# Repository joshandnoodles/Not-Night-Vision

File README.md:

## Objective

Using a PIC microcontroller and a non-contact infrared thermometer, MLX90614, an extremely low-cost thermal imaging system can be realized at a price point where thermal imaging data will be able to supplement and potentially replace traditional imaging solutions. The small, low cost MLX90614’s high precision measurements along with its narrow field of view (5&deg;) allow for cheap thermal data at a resolution that was previously unimaginable. Existing thermal imaging concepts using this sensor have already seen success[^ir_eye] [^arduino_ex]. However, the benefits of this sensor can be further exploited by using the following devices: mirrors to reduce vibrations and increase tracking speed, optics/diaphragm to precisely change pixel size for objects of varying size or varying distances, sampling and interpolation techniques, and low-level software changes to enhance sensor’s data collection. 

[^ir_eye]: http://spectrum.ieee.org/geek-life/hands-on/ir-eye

[^arduino_ex]: http://community.wolfram.com/groups/-/m/t/246929

[^pic_prod_list]: http://www.microchip.com/ParamChartSearch/Chart.aspx?branchID=8187

[^mlx_prod]: http://www.melexis.com/Infrared-Thermometer-Sensors/Infrared-Thermometer-Sensors/MLX90614-615.aspx

## Evaluation

At the conclusion of the project, success will be determined based on the system’s ability to complete the following tasks:

1. Reconstruct a 64-pixel image of a glass of heated water placed 10 meters away 
	- Temperature accuracy of +/1&deg;F
	- Image capture time <= 60 sec
2. Track a designated person moving at walking speed in a room maintaining tracking on that person even with other non-moving people in the room
	- *This will not necessarily be completed on the similar timeline as Task 1. It is an extra evaluation standard most likely meant for future time.*

## Project Needs

Hardware, tools, supplies anticipated for project:
- PIC microcontroller  with I2C capabilities to connect with IR sensor
- MLX90614 sensor 
- Soldering tools
- Custom PCB (additional components for standalone system to be determined)

## Team Roster

Joshua Alexander – Hardware/Software 
[id]: https://www.dropbox.com/s/68cuoj26z9y5twk/thermal_img_man.png?raw=1 "Figure 1: never "

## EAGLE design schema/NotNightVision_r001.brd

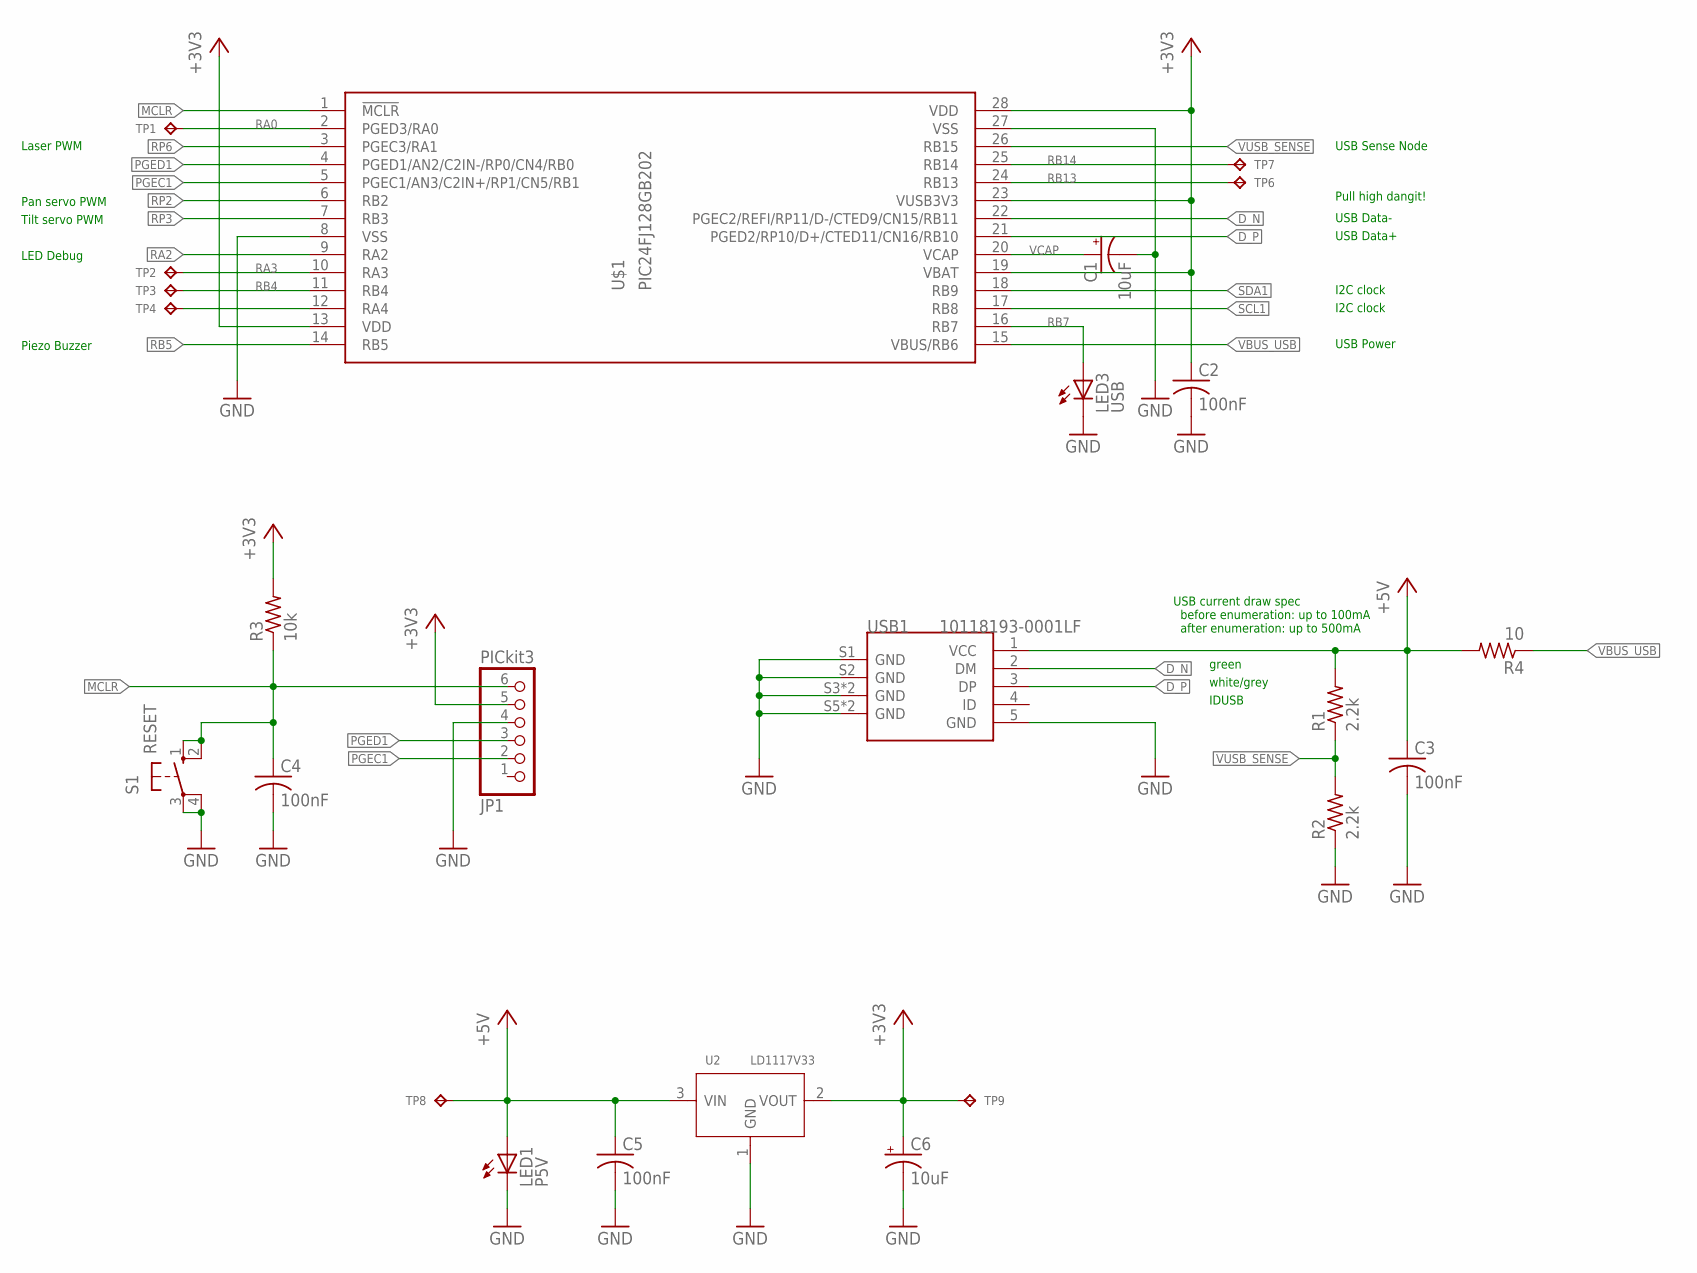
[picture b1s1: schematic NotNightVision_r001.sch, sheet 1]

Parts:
C1, C6: 10uF; TT5D10
C2, C3, C4, C5: 100nF; C025-025X050
JP1: PICkit3; 1X06/90
LED1: P5V; LED5MM
LED3: USB; LED3MM
R1, R2: 2.2k; 0207/7
R3: 10k; 0207/7
R4: 10; 0207/7
S1: RESET; B3F-10XX
TP1, TP2, TP3, TP4, TP6, TP7, TP8, TP9: TP10; 10MIL_ROUND
U2: LD1117V33; TO-220V
U$1: PIC24FJ128GB202; DIL28-3
USB1: 10118193-0001LF; MICRO-USB5+6P-SMD-0.65-B

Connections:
+3V3: C2.1, C6.+, JP1.5, R3.2, TP9.TP, U2.2 (VOUT), U$1.13 (VDD), U$1.19 (VBAT), U$1.23 (VUSB3V3), U$1.28 (VDD); also elsewhere on the board
+5V: C3.1, C5.1, LED1.A, R1.2, R4.2, TP8.TP, U2.3 (VIN), USB1.1 (VCC); also elsewhere on the board
D_N: U$1.22 (PGEC2/REFI/RP11/D-/CTED9/CN15/RB11), USB1.2 (DM)
D_P: U$1.21 (PGED2/RP10/D+/CTED11/CN16/RB10), USB1.3 (DP)
GND: C1.-, C2.2, C3.2, C4.2, C5.2, C6.-, JP1.4, LED1.K (C), LED3.K (C), R2.1, S1.3, S1.4 (P1), U2.1 (GND), U$1.8 (VSS), U$1.27 (VSS), USB1.5 (GND), USB1.S1 (GND), USB1.S2 (GND), USB1.S3 (GND), USB1.S4 (GND), USB1.S5 (GND), USB1.S6 (GND); also elsewhere on the board
MCLR: C4.1, JP1.6, R3.1, S1.1 (S), S1.2 (S1), U$1.1 (!MCLR)
PGEC1: JP1.2, U$1.5 (PGEC1/AN3/C2IN+/RP1/CN5/RB1)
PGED1: JP1.3, U$1.4 (PGED1/AN2/C2IN-/RP0/CN4/RB0)
RA0: TP1.TP, U$1.2 (PGED3/RA0)
RA2: U$1.9 (RA2); also elsewhere on the board
RA3: TP2.TP, U$1.10 (RA3)
RA4: TP4.TP, U$1.12 (RA4)
RB4: TP3.TP, U$1.11 (RB4)
RB5: U$1.14 (RB5); also elsewhere on the board
RB7: LED3.A, U$1.16 (RB7)
RB13: TP6.TP, U$1.24 (RB13)
RB14: TP7.TP, U$1.25 (RB14)
RP2: U$1.6 (RB2); also elsewhere on the board
RP3: U$1.7 (RB3); also elsewhere on the board
RP6: U$1.3 (PGEC3/RA1); also elsewhere on the board
SCL1: U$1.17 (RB8); also elsewhere on the board
SDA1: U$1.18 (RB9); also elsewhere on the board
VBUS_USB: R4.1, U$1.15 (VBUS/RB6)
VCAP: C1.+, U$1.20 (VCAP)
VUSB_SENSE: R1.1, R2.2, U$1.26 (RB15)

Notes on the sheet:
USB current draw spec before enumeration: up to 100mA after enumeration: up to 500mA
I2C clock
Pan servo PWM
Tilt servo PWM
Laser PWM
LED Debug
USB Data+
USB Data-
USB Sense Node
USB Power
Piezo Buzzer
green
white/grey
IDUSB
Pull high dangit!

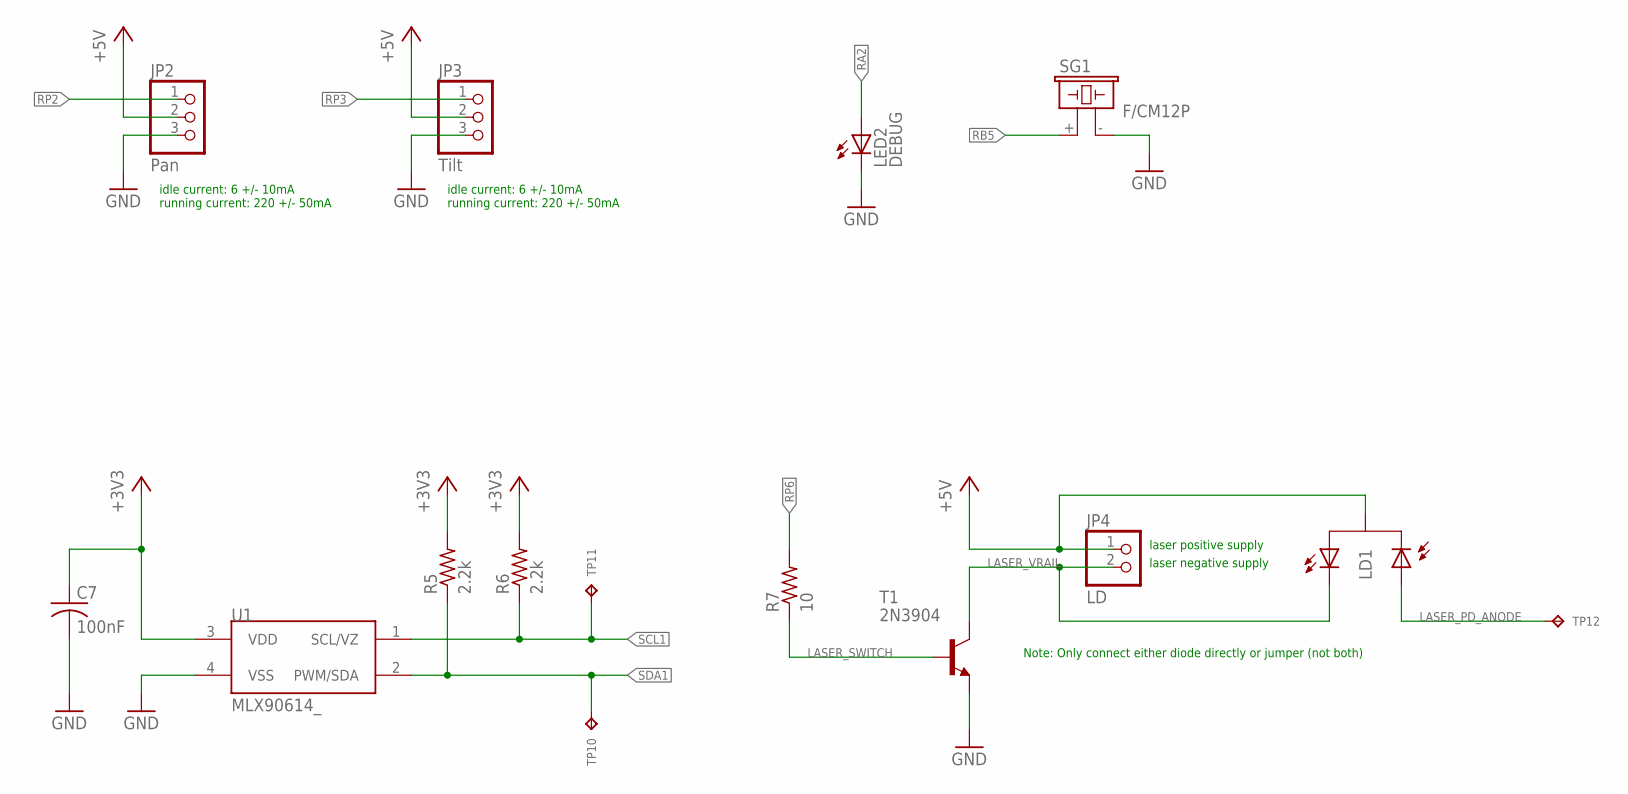
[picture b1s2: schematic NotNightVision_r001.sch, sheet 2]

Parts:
C7: 100nF; C025-025X050
JP2: Pan; 1X03
JP3: Tilt; 1X03
JP4: LD; 1X02
LD1: LASER_DIODE; TO-18
LED2: DEBUG; LED3MM
R5, R6: 2.2k; 0207/7
R7: 10; 0207/7
SG1: F/CM12P
T1: 2N3904; TO92
TP10, TP11, TP12: TP10; 10MIL_ROUND
U1: MLX90614_; TO-39; MPN 1747

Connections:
+3V3: C7.1, R5.2, R6.2, U1.3 (VDD); also elsewhere on the board
+5V: JP2.2, JP3.2, JP4.1, LD1.2 (V); also elsewhere on the board
GND: C7.2, JP2.3, JP3.3, LED2.K (C), SG1.- (2), T1.3 (E), U1.4 (VSS); also elsewhere on the board
LASER_PD_ANODE: LD1.3 (D+), TP12.TP
LASER_SWITCH: R7.1, T1.2 (B)
LASER_VRAIL: JP4.2, LD1.1 (D-), T1.1 (C)
RA2: LED2.A; also elsewhere on the board
RB5: SG1.+ (1); also elsewhere on the board
RP2: JP2.1; also elsewhere on the board
RP3: JP3.1; also elsewhere on the board
RP6: R7.2; also elsewhere on the board
SCL1: R6.1, TP11.TP, U1.1 (SCL/VZ); also elsewhere on the board
SDA1: R5.1, TP10.TP, U1.2 (PWM/SDA); also elsewhere on the board

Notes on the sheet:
idle current: 6 +/- 10mA running current: 220 +/- 50mA
laser positive supply
laser negative supply
Note: Only connect either diode directly or jumper (not both)

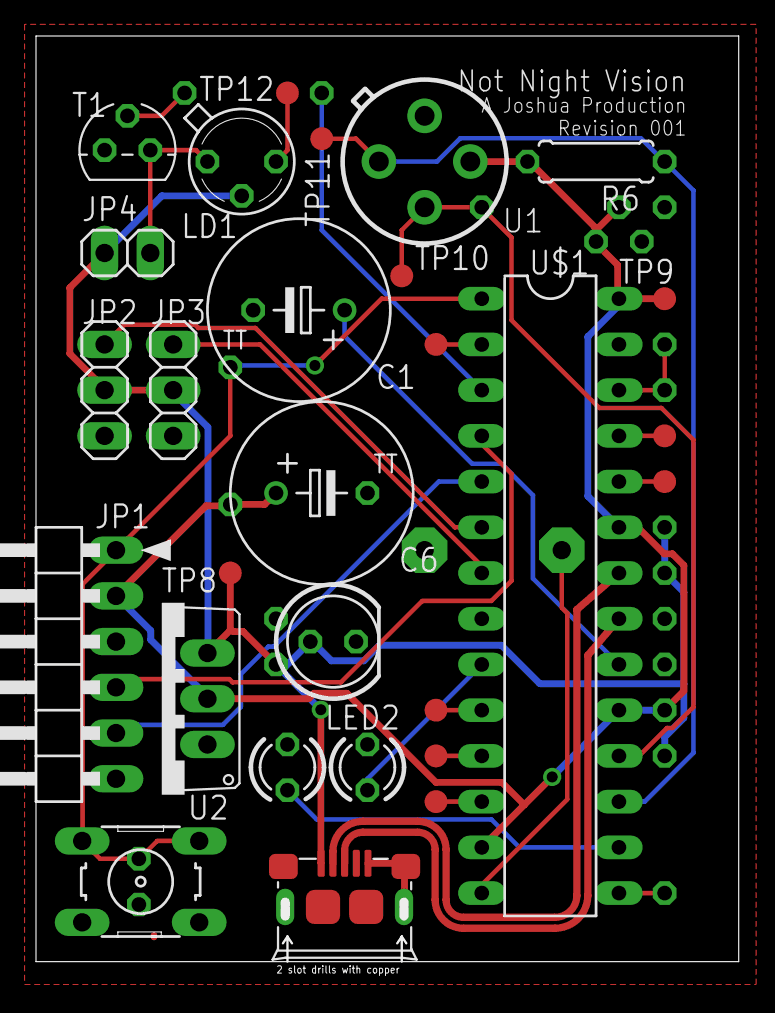
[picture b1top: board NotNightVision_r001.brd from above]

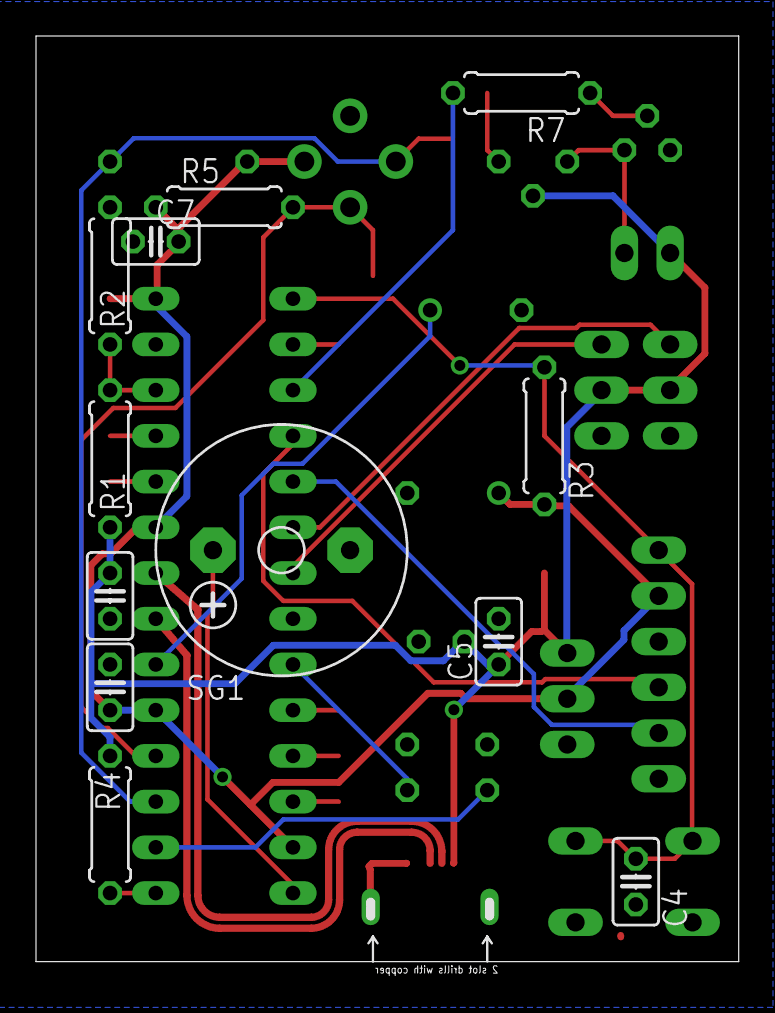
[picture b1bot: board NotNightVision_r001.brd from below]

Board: 2 copper layers, 38.5 x 51.8 mm, 40 parts (12 on the bottom side), 28 nets.

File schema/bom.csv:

"Qty","Value","Device","Package","Parts","Description","MF","MPN","OC_FARNELL","OC_NEWARK","TP_SIGNAL_NAME","VALUE",
"11","","TP10","10MIL_ROUND","TP1, TP2, TP3, TP4, TP6, TP7, TP8, TP9, TP10, TP11, TP12","Test pad","","","","","","",
"2","10","R-US_0207/7","0207/7","R4, R7","RESISTOR, American symbol","","","","unknown","","",
"5","100nF","C-US025-025X050","C025-025X050","C2, C3, C4, C5, C7","CAPACITOR, American symbol","","","","unknown","","",
"1","10118193-0001LF","MICRO-USB-SMD-B-(10118193-0001LF)","MICRO-USB5+6P-SMD-0.65-B","USB1","320010003","","10118193-0001LF","","67T2259","","10118193-0001LF",
"1","10k","R-US_0207/7","0207/7","R3","RESISTOR, American symbol","","","","unknown","","",
"2","10uF","CPOL-USTT5D10","TT5D10","C1, C6","POLARIZED CAPACITOR, American symbol","","","","unknown","","",
"4","2.2k","R-US_0207/7","0207/7","R1, R2, R5, R6","RESISTOR, American symbol","","","","unknown","","",
"1","2N3904","2N3904","TO92","T1","NPN TRANSISTOR","","","","","","",
"1","DEBUG","LED3MM","LED3MM","LED2","LED","","","","","","",
"1","F/CM12P","F/CM12P","F/CM12P","SG1","BUZZER Source: Buerklin","","","unknown","unknown","","",
"1","LASER_DIODE","LASER_DIODE","TO-18","LD1","","","","","","","",
"1","LD","PINHD-1X2","1X02","JP4","PIN HEADER","","","","","","",
"1","LD1117V33","LD1117V33TO220V","TO-220V","U2","310030025","","","","","","",
"1","MLX90614_","MLX90614_","TO-39","U1","Non-contact PIR I2C interface temperature sensor","","1747","","28Y4967","","",
"1","P5V","LED5MM","LED5MM","LED1","LED","","","","","","",
"1","PIC24FJ128GB202","PIC24FJ128GB202","DIL28-3","U$1","","","","","unknown","","",
"1","PICkit3","PINHD-1X6/90","1X06/90","JP1","PIN HEADER","","","","","","",
"1","Pan","PINHD-1X3","1X03","JP2","PIN HEADER","","","","","","",
"1","RESET","10-XX","B3F-10XX","S1","OMRON SWITCH","","B3F-1000","176432","36M3542","","",
"1","Tilt","PINHD-1X3","1X03","JP3","PIN HEADER","","","","","","",
"1","USB","LED3MM","LED3MM","LED3","LED","","","","","","",

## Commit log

2016-04-06 Updated Markdown documentation
2016-04-07 Added files via upload
2016-11-20 good node, pre-addition of toolbox
2016-11-20 ignore exported doc formates
2016-11-20 ignore exported doc formats"
2016-11-20 ignore exported doc formats
2016-11-21 added toolbox behavior to right side bar
2017-01-29 updates for better chrome app debug interface, graphing, controls, etc.
2017-01-29 general file cleanup
2017-02-20 restructered directories
2017-02-20 minor cosmetric changes
2017-02-20 updated documenation for current project state

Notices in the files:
parts and their libraries:
SparkFun-Sensors: Licensing: Creative Commons ShareAlike 4.0 International - https://creativecommons.org/licenses/by-sa/4.0
